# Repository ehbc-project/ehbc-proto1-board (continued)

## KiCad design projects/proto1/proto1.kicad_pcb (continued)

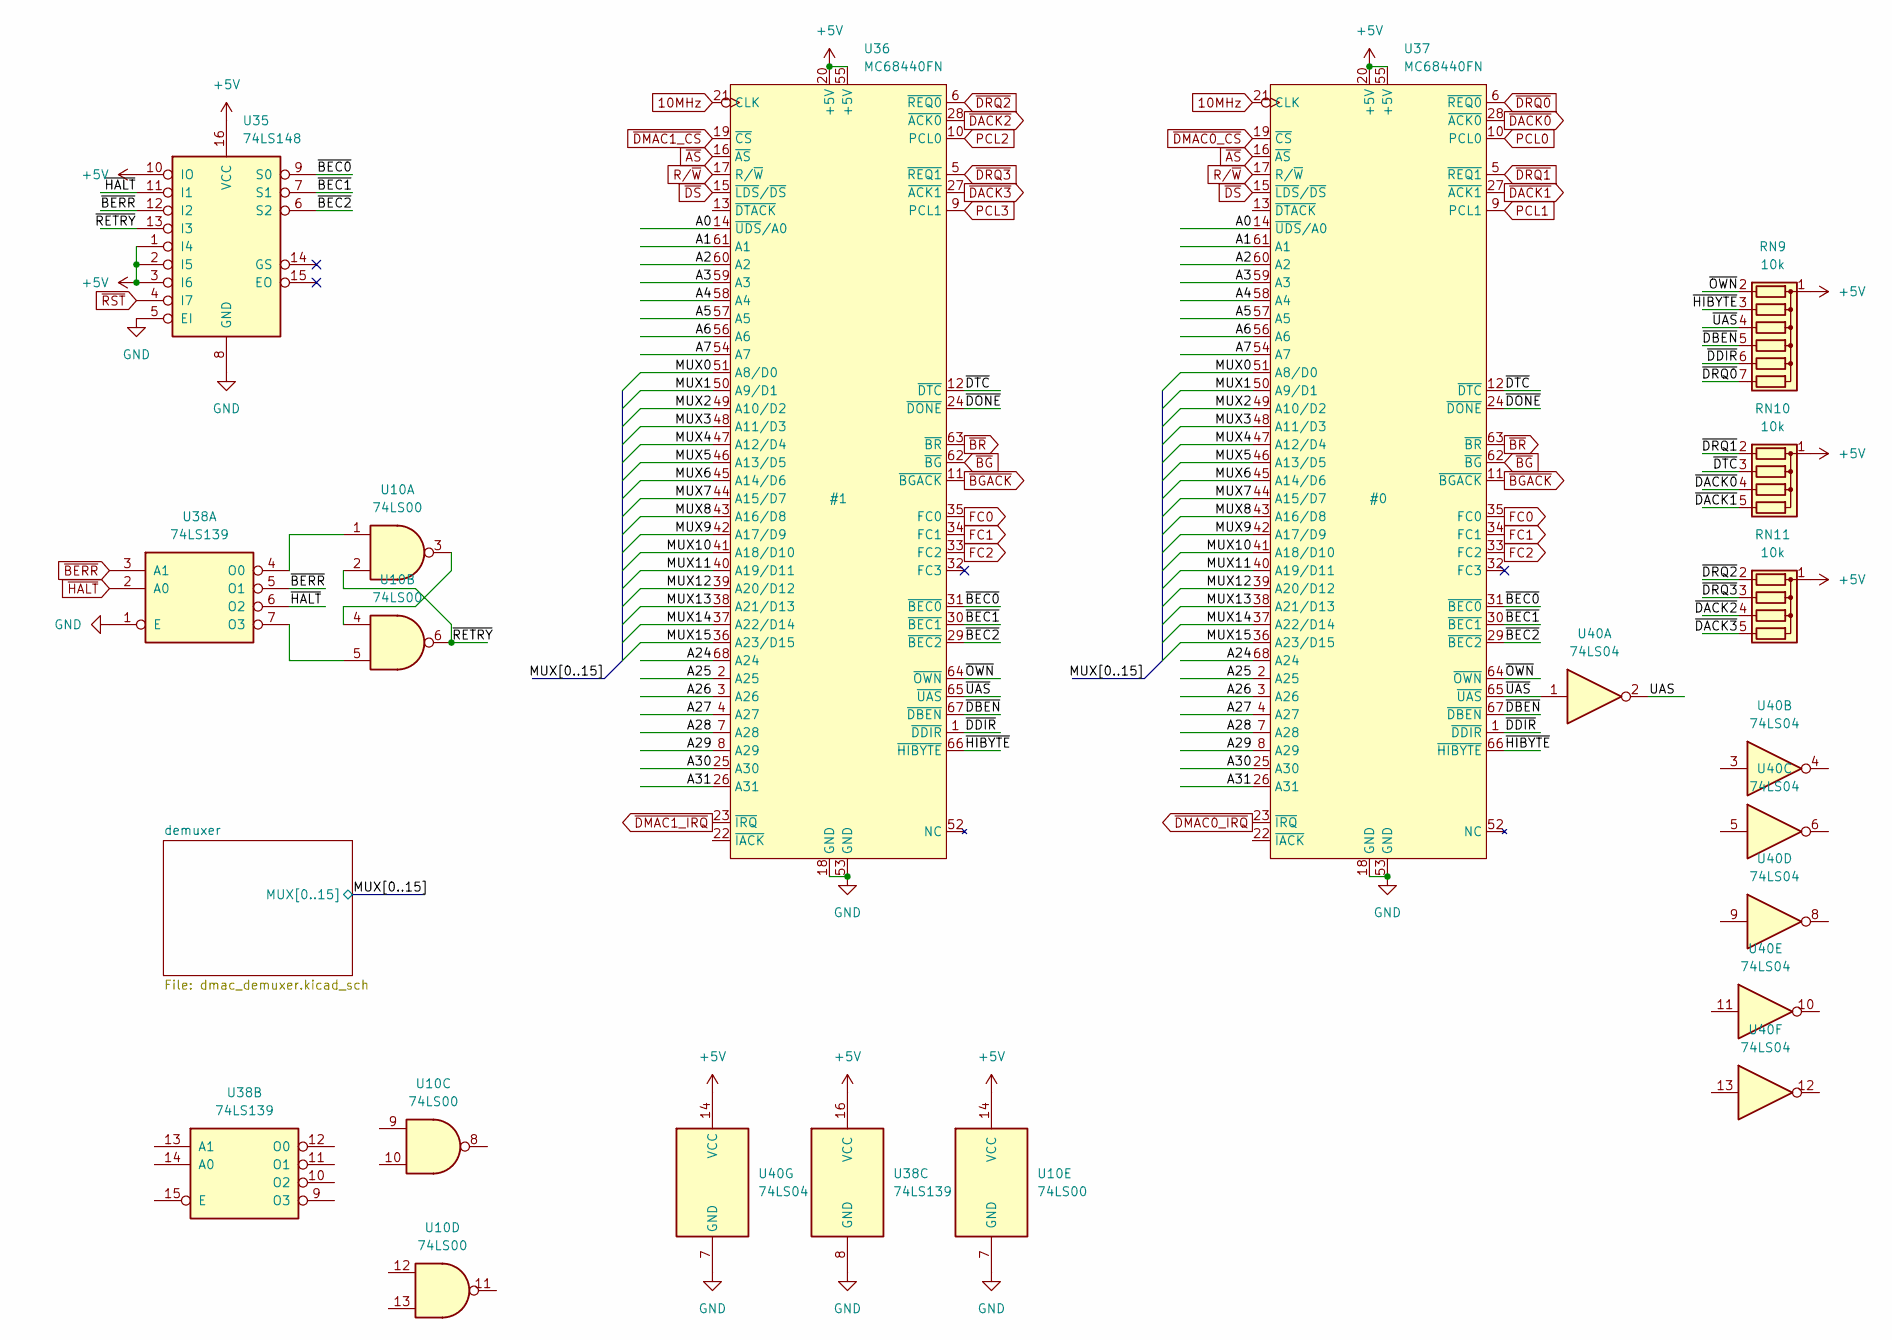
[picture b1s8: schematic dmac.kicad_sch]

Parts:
RN9: 10k; R_Array_SIP7
RN10, RN11: 10k; R_Array_SIP5
U10: 74LS00
U35: 74LS148; DIP-16_W7.62mm_Socket
U36, U37: MC68440FN; PLCC-68_THT-Socket
U38: 74LS139; DIP-16_W7.62mm_Socket
U40: 74LS04; DIP-14_W7.62mm_Socket

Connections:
10MHz: U36.21 (CLK), U37.21 (CLK); also elsewhere on the board
+5V: RN9.1 (common), RN10.1 (common), RN11.1 (common), U10.14 (VCC), U35.1 (I4), U35.2 (I5), U35.3 (I6), U35.10 (IO), U35.16 (VCC), U36.20 (+5V), U36.55 (+5V), U37.20 (+5V), U37.55 (+5V), U38.16 (VCC), U40.14 (VCC); also elsewhere on the board
/dmac/A0: U36.14 (~UDS/A0), U37.14 (~UDS/A0)
/dmac/A1: U36.61 (A1), U37.61 (A1)
/dmac/A2: U36.60 (A2), U37.60 (A2)
/dmac/A3: U36.59 (A3), U37.59 (A3)
/dmac/A4: U36.58 (A4), U37.58 (A4)
/dmac/A5: U36.57 (A5), U37.57 (A5)
/dmac/A6: U36.56 (A6), U37.56 (A6)
/dmac/A7: U36.54 (A7), U37.54 (A7)
/dmac/A24: U36.68 (A24), U37.68 (A24)
/dmac/A25: U36.2 (A25), U37.2 (A25)
/dmac/A26: U36.3 (A26), U37.3 (A26)
/dmac/A27: U36.4 (A27), U37.4 (A27)
/dmac/A28: U36.7 (A28), U37.7 (A28)
/dmac/A29: U36.8 (A29), U37.8 (A29)
/dmac/A30: U36.25 (A30), U37.25 (A30)
/dmac/A31: U36.26 (A31), U37.26 (A31)
/dmac/MUX0: U36.51 (A8/D0), U37.51 (A8/D0); also elsewhere on the board
/dmac/MUX1: U36.50 (A9/D1), U37.50 (A9/D1); also elsewhere on the board
/dmac/MUX2: U36.49 (A10/D2), U37.49 (A10/D2); also elsewhere on the board
/dmac/MUX3: U36.48 (A11/D3), U37.48 (A11/D3); also elsewhere on the board
/dmac/MUX4: U36.47 (A12/D4), U37.47 (A12/D4); also elsewhere on the board
/dmac/MUX5: U36.46 (A13/D5), U37.46 (A13/D5); also elsewhere on the board
/dmac/MUX6: U36.45 (A14/D6), U37.45 (A14/D6); also elsewhere on the board
/dmac/MUX7: U36.44 (A15/D7), U37.44 (A15/D7); also elsewhere on the board
/dmac/MUX8: U36.43 (A16/D8), U37.43 (A16/D8); also elsewhere on the board
/dmac/MUX9: U36.42 (A17/D9), U37.42 (A17/D9); also elsewhere on the board
/dmac/MUX10: U36.41 (A18/D10), U37.41 (A18/D10); also elsewhere on the board
/dmac/MUX11: U36.40 (A19/D11), U37.40 (A19/D11); also elsewhere on the board
/dmac/MUX12: U36.39 (A20/D12), U37.39 (A20/D12); also elsewhere on the board
/dmac/MUX13: U36.38 (A21/D13), U37.38 (A21/D13); also elsewhere on the board
/dmac/MUX14: U36.37 (A22/D14), U37.37 (A22/D14); also elsewhere on the board
/dmac/MUX15: U36.36 (A23/D15), U37.36 (A23/D15); also elsewhere on the board
/dmac/UAS: U40.2
/dmac/~BEC0: U35.9 (S0), U36.31 (~BEC0), U37.31 (~BEC0)
/dmac/~BEC1: U35.7 (S1), U36.30 (~BEC1), U37.30 (~BEC1)
/dmac/~BEC2: U35.6 (S2), U36.29 (~BEC2), U37.29 (~BEC2)
/dmac/~DBEN: RN9.5 (R4), U36.67 (~DBEN), U37.67 (~DBEN)
/dmac/~DDIR: RN9.6 (R5), U36.1 (~DDIR), U37.1 (~DDIR)
/dmac/~DONE: U36.24 (~DONE), U37.24 (~DONE)
/dmac/~DTC: RN10.3 (R2), U36.12 (~DTC), U37.12 (~DTC)
/dmac/~HIBYTE: RN9.3 (R2), U36.66 (~HIBYTE), U37.66 (~HIBYTE)
/dmac/~OWN: RN9.2 (R1), U36.64 (~OWN), U37.64 (~OWN)
/dmac/~RETRY: U10.2, U10.6, U35.13 (I3)
/dmac/~UAS: RN9.4 (R3), U36.65 (~UAS), U37.65 (~UAS), U40.1
FC0: U36.35 (FC0), U37.35 (FC0); also elsewhere on the board
FC1: U36.34 (FC1), U37.34 (FC1); also elsewhere on the board
FC2: U36.33 (FC2), U37.33 (FC2); also elsewhere on the board
GND: U10.7 (GND), U35.5 (EI), U35.8 (GND), U36.18 (GND), U36.53 (GND), U37.18 (GND), U37.53 (GND), U38.1 (E), U38.8 (GND), U40.7 (GND); also elsewhere on the board
unnamed: U10.3, U10.4
unnamed: U10.1, U38.4 (O0)
unnamed: U10.5, U38.7 (O3)
PCL0: U37.10 (PCL0)
PCL1: U37.9 (PCL1)
PCL2: U36.10 (PCL0)
PCL3: U36.9 (PCL1)
R/~W: U36.17 (R/~W), U37.17 (R/~W); also elsewhere on the board
~AS: U36.16 (~AS), U37.16 (~AS); also elsewhere on the board
~BERR: U35.12 (I2), U38.3 (A1), U38.5 (O1); also elsewhere on the board
~BGACK: U36.11 (~BGACK), U37.11 (~BGACK); also elsewhere on the board
~BG: U36.62 (~BG), U37.62 (~BG); also elsewhere on the board
~BR: U36.63 (~BR), U37.63 (~BR); also elsewhere on the board
~DACK0: RN10.4 (R3), U37.28 (~ACK0)
~DACK1: RN10.5 (R4), U37.27 (~ACK1)
~DACK2: RN11.4 (R3), U36.28 (~ACK0)
~DACK3: RN11.5 (R4), U36.27 (~ACK1)
~DMAC0_CS: U37.19 (~CS)
~DMAC0_IRQ: U37.23 (~IRQ); also elsewhere on the board
~DMAC1_CS: U36.19 (~CS)
~DMAC1_IRQ: U36.23 (~IRQ); also elsewhere on the board
~DRQ0: RN9.7 (R6), U37.6 (~REQ0)
~DRQ1: RN10.2 (R1), U37.5 (~REQ1)
~DRQ2: RN11.2 (R1), U36.6 (~REQ0)
~DRQ3: RN11.3 (R2), U36.5 (~REQ1)
~DS: U10.10, U36.15 (~LDS/~DS), U37.15 (~LDS/~DS); also elsewhere on the board
~DUART_CS: U10.9
~HALT: U35.11 (I1), U38.2 (A0), U38.6 (O2); also elsewhere on the board
~RST: U35.4 (I7); also elsewhere on the board

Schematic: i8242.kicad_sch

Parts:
C23: 100n; C_Disc_D4.3mm_W1.9mm_P5.00mm
J7: KMDGX-6SG_P-S4N; KMDGX6SGPS4N; Mouser Part Number 806-KMDGX-6SGP-S4N
U14: VT82C42; DIP-40_W15.24mm_Socket

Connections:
8MHz: U14.3 (XTAL2); also elsewhere on the board
+5V: C23.1, U14.40 (+5V); also elsewhere on the board
/i8242/BA0: U14.9 (A0)
/i8242/BD24: U14.12 (D0)
/i8242/BD25: U14.13 (D1)
/i8242/BD26: U14.14 (D2)
/i8242/BD27: U14.15 (D3)
/i8242/BD28: U14.16 (D4)
/i8242/BD29: U14.17 (D5)
/i8242/BD30: U14.18 (D6)
/i8242/BD31: U14.19 (D7)
GND: C23.2, U14.2 (XTAL1), U14.20 (GND); also elsewhere on the board
KB_IRQ: U14.35 (P24); also elsewhere on the board
MS_IRQ: U14.36 (P25); also elsewhere on the board
~I8242_CS: U14.6 (~CS)
~RD: U14.8 (~RD); also elsewhere on the board
~RST: U14.4 (~RST); also elsewhere on the board
~WR: U14.10 (~WR); also elsewhere on the board

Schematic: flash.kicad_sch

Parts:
C9, C10: 100n; C_Disc_D4.3mm_W1.9mm_P5.00mm
U7, U8: SST39SF040; DIP-32_W15.24mm_Socket

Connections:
+5V: C9.1, C10.1, U7.32 (VCC), U8.32 (VCC); also elsewhere on the board
A1: U7.12 (A0), U8.12 (A0); also elsewhere on the board
A2: U7.11 (A1), U8.11 (A1); also elsewhere on the board
A3: U7.10 (A2), U8.10 (A2); also elsewhere on the board
A4: U7.9 (A3), U8.9 (A3); also elsewhere on the board
A5: U7.8 (A4), U8.8 (A4); also elsewhere on the board
A6: U7.7 (A5), U8.7 (A5); also elsewhere on the board
A7: U7.6 (A6), U8.6 (A6); also elsewhere on the board
A8: U7.5 (A7), U8.5 (A7); also elsewhere on the board
A9: U7.27 (A8), U8.27 (A8); also elsewhere on the board
A10: U7.26 (A9), U8.26 (A9); also elsewhere on the board
A11: U7.23 (A10), U8.23 (A10); also elsewhere on the board
A12: U7.25 (A11), U8.25 (A11); also elsewhere on the board
A13: U7.4 (A12), U8.4 (A12); also elsewhere on the board
A14: U7.28 (A13), U8.28 (A13); also elsewhere on the board
A15: U7.29 (A14), U8.29 (A14); also elsewhere on the board
A16: U7.3 (A15), U8.3 (A15); also elsewhere on the board
A17: U7.2 (A16), U8.2 (A16); also elsewhere on the board
A18: U7.30 (A17), U8.30 (A17); also elsewhere on the board
A19: U7.1 (A18), U8.1 (A18); also elsewhere on the board
D16: U7.13 (D0); also elsewhere on the board
D17: U7.14 (D1); also elsewhere on the board
D18: U7.15 (D2); also elsewhere on the board
D19: U7.17 (D3); also elsewhere on the board
D20: U7.18 (D4); also elsewhere on the board
D21: U7.19 (D5); also elsewhere on the board
D22: U7.20 (D6); also elsewhere on the board
D23: U7.21 (D7); also elsewhere on the board
D24: U8.13 (D0); also elsewhere on the board
D25: U8.14 (D1); also elsewhere on the board
D26: U8.15 (D2); also elsewhere on the board
D27: U8.17 (D3); also elsewhere on the board
D28: U8.18 (D4); also elsewhere on the board
D29: U8.19 (D5); also elsewhere on the board
D30: U8.20 (D6); also elsewhere on the board
D31: U8.21 (D7); also elsewhere on the board
GND: C9.2, C10.2, U7.16 (GND), U7.24 (OE), U8.16 (GND), U8.24 (OE); also elsewhere on the board
~FLASH_CS: U7.22 (CE), U8.22 (CE)

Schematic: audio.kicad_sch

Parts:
C26, C27, C36, C37: 20p; C_Disc_D4.3mm_W1.9mm_P5.00mm
C28, C29, C32, C33, C34, C38, C40: 100n; C_Disc_D4.3mm_W1.9mm_P5.00mm
C30, C31, C35: 1u; CP_Radial_D5.0mm_P2.50mm
C39, C41: 10u; CP_Radial_D5.0mm_P2.50mm
C42, C43: 1n; C_Disc_D4.3mm_W1.9mm_P5.00mm
J11: AUDIO_DATA; PinHeader_2x05_P2.54mm_Vertical
J12: STX-4335-5BGP-S1; STX43355BGPS1; Mouser Part Number 806-STX-43355BGPS1
L1: L; L_Axial_L9.5mm_D4.0mm_P5.08mm_Vertical_Fastron_SMCC
R5: 2; R_Axial_DIN0204_L3.6mm_D1.6mm_P7.62mm_Horizontal
RN8: 33; DIP-8_W7.62mm
U26: CS4231A; PLCC-68_THT-Socket
Y2: 24.576M; Crystal_HC49-4H_Vertical
Y3: 16.9344M; Crystal_HC49-4H_Vertical

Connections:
+5V: C28.2, C29.2, C30.1, C31.1, J11.1, L1.1, U26.1 (VD1), U26.7 (VD2), U26.23 (~PDWN); also elsewhere on the board
+5VA: C34.1, C35.1, R5.2, U26.35 (VA1), U26.36 (VA2); also elsewhere on the board
/audio/BLUE_RING: J12.35; also elsewhere on the board
/audio/BLUE_TIP: J12.32; also elsewhere on the board
/audio/LIME_RING: J12.25; also elsewhere on the board
/audio/LIME_TIP: J12.22; also elsewhere on the board
/audio/LLINE: U26.30 (LLINE); also elsewhere on the board
/audio/LMIC: U26.29 (LMIC); also elsewhere on the board
/audio/PINK_RING: J12.5; also elsewhere on the board
/audio/PINK_TIP: J12.2; also elsewhere on the board
/audio/PWR1: C32.2, C33.2, L1.2, R5.1, U26.15 (VD3), U26.19 (VD4)
/audio/RLINE: U26.27 (RLINE); also elsewhere on the board
/audio/RMIC: U26.28 (RMIC); also elsewhere on the board
/audio/VREF: C40.2, C41.1, U26.32 (VREF); also elsewhere on the board
/audio/VREFI: C38.2, C39.1, U26.33 (VREFI)
/audio/XTAL1I: C36.2, U26.17 (XTAL1I), Y2.1
/audio/XTAL1O: C26.1, U26.18 (XTAL1O), Y2.2
/audio/XTAL2I: C37.2, U26.21 (XTAL2I), Y3.1
/audio/XTAL2O: C27.1, U26.22 (XTAL2O), Y3.2
AUDIO_IRQ: U26.57 (IRQ); also elsewhere on the board
BA0: U26.10 (A0); also elsewhere on the board
BA1: U26.9 (A1); also elsewhere on the board
BD24: U26.6 (D0); also elsewhere on the board
BD25: U26.5 (D1); also elsewhere on the board
BD26: U26.4 (D2); also elsewhere on the board
BD27: U26.3 (D3); also elsewhere on the board
BD28: U26.68 (D4); also elsewhere on the board
BD29: U26.67 (D5); also elsewhere on the board
BD30: U26.66 (D6); also elsewhere on the board
BD31: U26.65 (D7); also elsewhere on the board
GND: C26.2, C27.2, C28.1, C29.1, C30.2, C31.2, C36.1, C37.1, J11.2, J11.4, J11.6, J11.8, J11.10, U26.2 (DGND1), U26.8 (DGND2), U26.16 (DGND3), U26.20 (DGND4), U26.53 (DGND7), U26.55 (TEST), U26.64 (DGND8); also elsewhere on the board
GNDA: C32.1, C33.1, C34.2, C35.2, C38.1, C39.2, C40.1, C41.2, C42.2, C43.2, J12.1, J12.3, J12.4, J12.23, J12.24, J12.33, J12.34, J12.MH1, J12.MH2, J12.MH3, J12.MH4, U26.34 (AGND1), U26.37 (AGND2); also elsewhere on the board
unnamed: J11.3, RN8.8 (R1.2)
unnamed: J11.5, RN8.7 (R2.2)
unnamed: J11.7, RN8.6 (R3.2)
unnamed: J11.9, RN8.5 (R4.2)
unnamed: RN8.1 (R1.1), U26.52 (SDOUT)
unnamed: RN8.2 (R2.1), U26.51 (SCLK)
unnamed: RN8.3 (R3.1), U26.50 (FSYNC)
unnamed: RN8.4 (R4.1), U26.49 (SDIN)
unnamed: C43.1, U26.31 (LFILT)
unnamed: C42.1, U26.26 (RFILT)
~AUDIO_CS: U26.59 (~CS)
~RD: U26.60 (~RD); also elsewhere on the board
~WR: U26.61 (~WR); also elsewhere on the board

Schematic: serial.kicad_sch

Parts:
C11, C12, C14, C15, C16, C17, C18, C19: 1u; C_Disc_D4.3mm_W1.9mm_P5.00mm
C13: 100n; C_Disc_D4.3mm_W1.9mm_P5.00mm
J4, J5: 5747840-4; 57478404; Mouser Part Number 571-5747840-4
U9, U12: MAX232; DIP-16_W7.62mm_Socket
U11: MC68681P; DIP-40_W15.24mm_Socket

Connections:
3.6864MHz: U11.33 (X2); also elsewhere on the board
+5V: C13.1, U9.16 (VCC), U11.40 (VCC), U12.16 (VCC); also elsewhere on the board
/serial/RxDA: U9.12 (R1OUT), U11.31 (RxDA)
/serial/RxDB: U11.10 (RxDB), U12.12 (R1OUT)
/serial/RxDP1: J4.2, U9.13 (R1IN)
/serial/RxDP2: J5.2, U12.13 (R1IN)
/serial/TxDA: U9.11 (T1IN), U11.30 (TxDA)
/serial/TxDB: U11.11 (TxDB), U12.11 (T1IN)
/serial/TxDP1: J4.3, U9.14 (T1OUT)
/serial/TxDP2: J5.3, U12.14 (T1OUT)
/serial/~CTSA: U9.9 (R2OUT), U11.7 (IP0)
/serial/~CTSB: U11.4 (IP1), U12.9 (R2OUT)
/serial/~CTSP1: J4.8, U9.8 (R2IN)
/serial/~CTSP2: J5.8, U12.8 (R2IN)
/serial/~RTSA: U9.10 (T2IN), U11.29 (OP0)
/serial/~RTSB: U11.12 (OP1), U12.10 (T2IN)
/serial/~RTSP1: J4.7, U9.7 (T2OUT)
/serial/~RTSP2: J5.7, U12.7 (T2OUT)
BA0: U11.1 (RS1); also elsewhere on the board
BA1: U11.3 (RS2); also elsewhere on the board
BA2: U11.5 (RS3); also elsewhere on the board
BA3: U11.6 (RS4); also elsewhere on the board
BD24: U11.25 (D0); also elsewhere on the board
BD25: U11.16 (D1); also elsewhere on the board
BD26: U11.24 (D2); also elsewhere on the board
BD27: U11.17 (D3); also elsewhere on the board
BD28: U11.23 (D4); also elsewhere on the board
BD29: U11.18 (D5); also elsewhere on the board
BD30: U11.22 (D6); also elsewhere on the board
BD31: U11.19 (D7); also elsewhere on the board
GND: C13.2, C14.2, C15.2, C18.2, C19.2, J4.5, J5.5, U9.15 (GND), U11.20 (GND), U12.15 (GND); also elsewhere on the board
unnamed: C11.1, U9.1 (C1+)
unnamed: C11.2, U9.3 (C1-)
unnamed: C12.1, U9.4 (C2+)
unnamed: C12.2, U9.5 (C2-)
unnamed: C14.1, U9.2 (VS+)
unnamed: C15.1, U9.6 (VS-)
unnamed: C16.1, U12.1 (C1+)
unnamed: C16.2, U12.3 (C1-)
unnamed: C17.1, U12.4 (C2+)
unnamed: C17.2, U12.5 (C2-)
unnamed: C18.1, U12.2 (VS+)
unnamed: C19.1, U12.6 (VS-)
R/~W: U11.8 (R/~W); also elsewhere on the board
~DSACK0: U11.9 (~DTACK); also elsewhere on the board
~DUART_IRQ: U11.21 (~IRQ); also elsewhere on the board
~RST: U11.34 (~RST); also elsewhere on the board

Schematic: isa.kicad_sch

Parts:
J1, J2, J3: Bus_ISA_16bit; ATA_16bit
RN3: 10k; R_Array_SIP10
RN4: 4.7k; R_Array_SIP8
RN5, RN6: 4.7k; R_Array_SIP7

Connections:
8MHz: J1.20 (CLK), J2.20 (CLK), J3.20 (CLK); also elsewhere on the board
14.31818MHz: J1.30 (OSC), J2.30 (OSC), J3.30 (OSC); also elsewhere on the board
+5V: J1.3 (+5V), J1.29 (VCC), J1.78 (+5V), J2.3 (+5V), J2.29 (VCC), J2.78 (+5V), J3.3 (+5V), J3.29 (VCC), J3.78 (+5V), RN3.1 (common); also elsewhere on the board
+12V: J1.9 (+12V), J2.9 (+12V), J3.9 (+12V); also elsewhere on the board
-12V: J1.7 (-12V), J2.7 (-12V), J3.7 (-12V); also elsewhere on the board
/isa/ALE: J1.28 (ALE), J2.28 (ALE), J3.28 (ALE)
/isa/BA0: J1.62 (BA00), J2.62 (BA00), J3.62 (BA00); also elsewhere on the board
/isa/BA1: J1.61 (BA01), J2.61 (BA01), J3.61 (BA01); also elsewhere on the board
/isa/BA2: J1.60 (BA02), J2.60 (BA02), J3.60 (BA02); also elsewhere on the board
/isa/BA3: J1.59 (BA03), J2.59 (BA03), J3.59 (BA03); also elsewhere on the board
/isa/BA4: J1.58 (BA04), J2.58 (BA04), J3.58 (BA04); also elsewhere on the board
/isa/BA5: J1.57 (BA05), J2.57 (BA05), J3.57 (BA05); also elsewhere on the board
/isa/BA6: J1.56 (BA06), J2.56 (BA06), J3.56 (BA06); also elsewhere on the board
/isa/BA7: J1.55 (BA07), J2.55 (BA07), J3.55 (BA07); also elsewhere on the board
/isa/BA8: J1.54 (BA08), J2.54 (BA08), J3.54 (BA08); also elsewhere on the board
/isa/BA9: J1.53 (BA09), J2.53 (BA09), J3.53 (BA09); also elsewhere on the board
/isa/BA10: J1.52 (BA10), J2.52 (BA10), J3.52 (BA10); also elsewhere on the board
/isa/BA11: J1.51 (BA11), J2.51 (BA11), J3.51 (BA11); also elsewhere on the board
/isa/BA12: J1.50 (BA12), J2.50 (BA12), J3.50 (BA12); also elsewhere on the board
/isa/BA13: J1.49 (BA13), J2.49 (BA13), J3.49 (BA13); also elsewhere on the board
/isa/BA14: J1.48 (BA14), J2.48 (BA14), J3.48 (BA14); also elsewhere on the board
/isa/BA15: J1.47 (BA15), J2.47 (BA15), J3.47 (BA15); also elsewhere on the board
/isa/BA16: J1.46 (BA16), J2.46 (BA16), J3.46 (BA16); also elsewhere on the board
/isa/BA17: J1.45 (BA17), J1.88 (LA17), J2.45 (BA17), J2.88 (LA17), J3.45 (BA17), J3.88 (LA17); also elsewhere on the board
/isa/BA18: J1.44 (BA18), J1.87 (LA18), J2.44 (BA18), J2.87 (LA18), J3.44 (BA18), J3.87 (LA18); also elsewhere on the board
/isa/BA19: J1.43 (BA19), J1.86 (LA19), J2.43 (BA19), J2.86 (LA19), J3.43 (BA19), J3.86 (LA19); also elsewhere on the board
/isa/BA20: J1.85 (LA20), J2.85 (LA20), J3.85 (LA20); also elsewhere on the board
/isa/BA21: J1.84 (LA21), J2.84 (LA21), J3.84 (LA21); also elsewhere on the board
/isa/BA22: J1.83 (LA22), J2.83 (LA22), J3.83 (LA22); also elsewhere on the board
/isa/BA23: J1.82 (LA23), J2.82 (LA23), J3.82 (LA23); also elsewhere on the board
/isa/BD0: J1.40 (DB0), J2.40 (DB0), J3.40 (DB0); also elsewhere on the board
/isa/BD1: J1.39 (DB1), J2.39 (DB1), J3.39 (DB1); also elsewhere on the board
/isa/BD2: J1.38 (DB2), J2.38 (DB2), J3.38 (DB2); also elsewhere on the board
/isa/BD3: J1.37 (DB3), J2.37 (DB3), J3.37 (DB3); also elsewhere on the board
/isa/BD4: J1.36 (DB4), J2.36 (DB4), J3.36 (DB4); also elsewhere on the board
/isa/BD5: J1.35 (DB5), J2.35 (DB5), J3.35 (DB5); also elsewhere on the board
/isa/BD6: J1.34 (DB6), J2.34 (DB6), J3.34 (DB6); also elsewhere on the board
/isa/BD7: J1.33 (DB7), J2.33 (DB7), J3.33 (DB7); also elsewhere on the board
/isa/BD8: J1.91 (D8), J2.91 (D8), J3.91 (D8); also elsewhere on the board
/isa/BD9: J1.92 (D9), J2.92 (D9), J3.92 (D9); also elsewhere on the board
/isa/BD10: J1.93 (D10), J2.93 (D10), J3.93 (D10); also elsewhere on the board
/isa/BD11: J1.94 (D11), J2.94 (D11), J3.94 (D11); also elsewhere on the board
/isa/BD12: J1.95 (D12), J2.95 (D12), J3.95 (D12); also elsewhere on the board
/isa/BD13: J1.96 (D13), J2.96 (D13), J3.96 (D13); also elsewhere on the board
/isa/BD14: J1.97 (D14), J2.97 (D14), J3.97 (D14); also elsewhere on the board
/isa/BD15: J1.98 (D15), J2.98 (D15), J3.98 (D15); also elsewhere on the board
/isa/DRQ0: J1.71 (DRQ0), J2.71 (DRQ0), J3.71 (DRQ0), RN4.5 (R4)
/isa/DRQ1: J1.18 (DRQ1), J2.18 (DRQ1), J3.18 (DRQ1), RN4.6 (R5)
/isa/DRQ2: J1.6 (DRQ2), J2.6 (DRQ2), J3.6 (DRQ2), RN4.7 (R6)
/isa/DRQ3: J1.16 (DRQ3), J2.16 (DRQ3), J3.16 (DRQ3), RN4.8 (R7)
/isa/DRQ5: J1.73 (DRQ5), J2.73 (DRQ5), J3.73 (DRQ5), RN4.4 (R3)
/isa/DRQ6: J1.75 (DRQ6), J2.75 (DRQ6), J3.75 (DRQ6), RN4.3 (R2)
/isa/DRQ7: J1.77 (DRQ7), J2.77 (DRQ7), J3.77 (DRQ7), RN4.2 (R1)
/isa/IOCHRDY: J1.41 (IO_READY), J2.41 (IO_READY), J3.41 (IO_READY); also elsewhere on the board
/isa/SBHE: J1.81 (SBHE), J2.81 (SBHE), J3.81 (SBHE)
/isa/~DACK0: J1.70 (~DACK0), J2.70 (~DACK0), J3.70 (~DACK0), RN3.5 (R4)
/isa/~DACK1: J1.17 (~DACK1), J2.17 (~DACK1), J3.17 (~DACK1), RN3.8 (R7)
/isa/~DACK2: J1.26 (~DACK2), J2.26 (~DACK2), J3.26 (~DACK2), RN3.6 (R5)
/isa/~DACK3: J1.15 (~DACK3), J2.15 (~DACK3), J3.15 (~DACK3), RN3.9 (R8)
/isa/~DACK5: J1.72 (~DACK5), J2.72 (~DACK5), J3.72 (~DACK5), RN3.4 (R3)
/isa/~DACK6: J1.74 (~DACK6), J2.74 (~DACK6), J3.74 (~DACK6), RN3.3 (R2)
/isa/~DACK7: J1.76 (~DACK7), J2.76 (~DACK7), J3.76 (~DACK7), RN3.2 (R1)
/isa/~IOCHCK: J1.32 (IO), J2.32 (IO), J3.32 (IO)
/isa/~IOCS16: J1.64 (~IOCS16), J2.64 (~IOCS16), J3.64 (~IOCS16); also elsewhere on the board
/isa/~IOR: J1.14 (~IOR), J2.14 (~IOR), J3.14 (~IOR)
/isa/~IOW: J1.13 (~IOW), J2.13 (~IOW), J3.13 (~IOW)
/isa/~MASTER: J1.79 (MASTER), J2.79 (MASTER), J3.79 (MASTER), RN3.10 (R9)
/isa/~MEMCS16: J1.63 (~MEMCS16), J2.63 (~MEMCS16), J3.63 (~MEMCS16)
/isa/~MEMR: J1.89 (~MEMR), J2.89 (~MEMR), J3.89 (~MEMR)
/isa/~MEMW: J1.90 (~MEMW), J2.90 (~MEMW), J3.90 (~MEMW)
/isa/~NOWS: J1.8 (UNUSED), J2.8 (UNUSED), J3.8 (UNUSED)
/isa/~REFRESH: J1.19 (~REFRESH), J2.19 (~REFRESH), J3.19 (~REFRESH), RN3.7 (R6)
/isa/~SMEMR: J1.12 (~SMEMR), J2.12 (~SMEMR), J3.12 (~SMEMR)
/isa/~SMEMW: J1.11 (~SMEMW), J2.11 (~SMEMW), J3.11 (~SMEMW)
GND: J1.1 (GND), J1.10 (GND), J1.31 (GND), J1.42 (AEN), J1.80 (GND), J2.1 (GND), J2.10 (GND), J2.31 (GND), J2.42 (AEN), J2.80 (GND), J3.1 (GND), J3.10 (GND), J3.31 (GND), J3.42 (AEN), J3.80 (GND), RN4.1 (common), RN5.1 (common), RN6.1 (common); also elsewhere on the board
IRQ2: J1.4 (IRQ2), J2.4 (IRQ2), J3.4 (IRQ2), RN5.7 (R6); also elsewhere on the board
IRQ3: J1.25 (IRQ3), J2.25 (IRQ3), J3.25 (IRQ3), RN5.2 (R1); also elsewhere on the board
IRQ4: J1.24 (IRQ4), J2.24 (IRQ4), J3.24 (IRQ4), RN5.3 (R2); also elsewhere on the board
IRQ5: J1.23 (IRQ5), J2.23 (IRQ5), J3.23 (IRQ5), RN5.4 (R3); also elsewhere on the board
IRQ6: J1.22 (IRQ6), J2.22 (IRQ6), J3.22 (IRQ6), RN5.5 (R4); also elsewhere on the board
IRQ7: J1.21 (IRQ7), J2.21 (IRQ7), J3.21 (IRQ7), RN5.6 (R5); also elsewhere on the board
IRQ10: J1.65 (IRQ10), J2.65 (IRQ10), J3.65 (IRQ10), RN6.6 (R5); also elsewhere on the board
IRQ11: J1.66 (IRQ11), J2.66 (IRQ11), J3.66 (IRQ11), RN6.5 (R4); also elsewhere on the board
IRQ12: J1.67 (IRQ12), J2.67 (IRQ12), J3.67 (IRQ12), RN6.4 (R3); also elsewhere on the board
IRQ14: J1.69 (IRQ14), J2.69 (IRQ14), J3.69 (IRQ14), RN6.2 (R1); also elsewhere on the board
IRQ15: J1.68 (IRQ15), J2.68 (IRQ15), J3.68 (IRQ15), RN6.3 (R2); also elsewhere on the board
RST: J1.2 (RESET), J2.2 (RESET), J3.2 (RESET); also elsewhere on the board

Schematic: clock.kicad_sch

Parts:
C24: 47n; C_Disc_D4.3mm_W1.9mm_P5.00mm
U15: MX8315MC; DIP-14_W7.62mm_Socket
X1: 10M; Oscillator_DIP-14
X2: 4M; Oscillator_DIP-14
X3: 3.6864M; Oscillator_DIP-14
X4: 8M; Oscillator_DIP-14
Y1: 14.31818M; Crystal_HC49-4H_Vertical

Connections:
3.6864MHz: X3.8 (OUT); also elsewhere on the board
4MHz: X2.8 (OUT); also elsewhere on the board
8MHz: X4.8 (OUT); also elsewhere on the board
10MHz: X1.8 (OUT); also elsewhere on the board
14.31818MHz: U15.4 (XCK); also elsewhere on the board
24MHz: U15.5 (PCK); also elsewhere on the board
+5V: U15.9 (DVDD), U15.14 (AVDD), X1.14 (Vcc); also elsewhere on the board
FREQ_SEL0: U15.11 (S0)
FREQ_SEL1: U15.12 (S1)
FREQ_SEL2: U15.13 (S2)
GND: C24.2, U15.1 (AGND), U15.7 (DGND), X1.7 (GND); also elsewhere on the board
unnamed: C24.1, U15.10 (CAP)
PROC_CLK: U15.8 (CK); also elsewhere on the board

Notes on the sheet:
MC68030@25/33/50MHz MC68882@=MC68030 MC68681@3.6864MHz MC68901@=MC68681 MC68440@10MHz MC146818@32.768kHz PC8477BV@24MHz VT82C42@12MHz MX8315MC@14.31818MHz ISABUS@8MHz 3.6864MHz 14.31818MHz -> 25/33/50Mhz, 12MHz, 24MHz, 8MHz 32.768kHz 10MHz

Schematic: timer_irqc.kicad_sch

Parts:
J9: TIMER0-3; PinHeader_1x05_P2.54mm_Vertical
J10: TIMER4-7; PinHeader_1x05_P2.54mm_Vertical
RN7: 10k; R_Array_SIP9
U20: 74LS348; DIP-16_W7.62mm_Socket
U21, U22: MC68901P; DIP-48_W15.24mm_Socket

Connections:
3.6864MHz: U21.17 (XTAL1), U22.17 (XTAL1); also elsewhere on the board
4MHz: U21.35 (CLK), U22.35 (CLK); also elsewhere on the board
+5V: RN7.1 (common), U20.10 (0), U20.16 (VCC), U21.11 (VCC), U22.11 (VCC); also elsewhere on the board
/timer_irqc/T0OUT: J9.1
/timer_irqc/T1OUT: J9.2
/timer_irqc/T2OUT: J9.3
/timer_irqc/T3OUT: J9.4
/timer_irqc/T4OUT: J10.1
/timer_irqc/T5OUT: J10.2
/timer_irqc/T6OUT: J10.3
/timer_irqc/T7OUT: J10.4
/timer_irqc/~IEO0: U21.33 (~IEO), U22.34 (~IEI)
/timer_irqc/~IRQ0: RN7.2 (R1)
/timer_irqc/~IRQ1: RN7.3 (R2), U20.11 (1)
/timer_irqc/~IRQ7: RN7.9 (R8), U20.4 (7)
AUDIO_IRQ: RN7.5 (R4), U20.13 (3); also elsewhere on the board
BA0: U21.2 (RS1), U22.2 (RS1); also elsewhere on the board
BA1: U21.3 (RS2), U22.3 (RS2); also elsewhere on the board
BA2: U21.4 (RS3), U22.4 (RS3); also elsewhere on the board
BA3: U21.5 (RS4), U22.5 (RS4); also elsewhere on the board
BA4: U21.6 (RS5), U22.6 (RS5)
BD24: U21.37 (D0), U22.37 (D0); also elsewhere on the board
BD25: U21.38 (D1), U22.38 (D1); also elsewhere on the board
BD26: U21.39 (D2), U22.39 (D2); also elsewhere on the board
BD27: U21.40 (D3), U22.40 (D3); also elsewhere on the board
BD28: U21.41 (D4), U22.41 (D4); also elsewhere on the board
BD29: U21.42 (D5), U22.42 (D5); also elsewhere on the board
BD30: U21.43 (D6), U22.43 (D6); also elsewhere on the board
BD31: U21.44 (D7), U22.44 (D7); also elsewhere on the board
FDC_IRQ: U21.29 (I7)
GND: J9.5, J10.5, U20.5 (EI), U20.8 (GND), U21.34 (~IEI), U21.36 (GND), U22.36 (GND); also elsewhere on the board
IDE_IRQ: U21.28 (I6)
IRQ2: U21.27 (I5); also elsewhere on the board
IRQ3: U22.26 (I4); also elsewhere on the board
IRQ4: U22.25 (I3); also elsewhere on the board
IRQ5: U22.24 (I2); also elsewhere on the board
IRQ6: U22.23 (I1); also elsewhere on the board
IRQ7: U22.22 (I0); also elsewhere on the board
IRQ10: U21.26 (I4); also elsewhere on the board
IRQ11: U21.25 (I3); also elsewhere on the board
IRQ12: U21.24 (I2); also elsewhere on the board
IRQ14: U21.23 (I1); also elsewhere on the board
IRQ15: U21.22 (I0); also elsewhere on the board
KB_IRQ: U22.29 (I7); also elsewhere on the board
MS_IRQ: U22.28 (I6); also elsewhere on the board
R/~W: U21.1 (R/~W), U22.1 (R/~W); also elsewhere on the board
~DMAC0_IRQ: RN7.7 (R6), U20.2 (5); also elsewhere on the board
~DMAC1_IRQ: RN7.6 (R5), U20.1 (4); also elsewhere on the board
~DSACK0: U21.46 (~DTACK), U22.46 (~DTACK); also elsewhere on the board
~DS: U21.47 (~DS), U22.47 (~DS); also elsewhere on the board
~DUART_IRQ: U22.27 (I5); also elsewhere on the board
~IPL0: U20.9 (A0); also elsewhere on the board
~IPL1: U20.7 (A1); also elsewhere on the board
~IPL2: U20.6 (A2); also elsewhere on the board
~MFP0_CS: U21.48 (~CS)
~MFP1_CS: U22.48 (~CS)
~MFP_IRQ: RN7.4 (R3), U20.12 (2), U21.32 (~IRQ), U22.32 (~IRQ)
~RST: U21.21 (~RST), U22.21 (~RST); also elsewhere on the board
~RTC_IRQ: RN7.8 (R7), U20.3 (6); also elsewhere on the board

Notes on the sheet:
PRIORITY: - MC68440 #0 - MC68440 #1 - MC68901 #0: - - PC8477BV - - IDE - - Timer 0 - - Timer 1 - - ISA INT2 - - ISA INT10 - - Timer 2 - - Timer 3 - - ISA INT11 - - ISA INT12 - - ISA INT14 - - ISA INT15 - MC68901 #1: - - VT82C42 KB - - VT82C42 MS - - Timer 4 - - Timer 5 - - MC68681 - - ISA INT3 - - 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

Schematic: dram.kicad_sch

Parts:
U3, U4, U5, U6: SIMM72

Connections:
+5V: U3.10 (+5V), U3.30 (+5V), U3.59 (+5V), U4.10 (+5V), U4.30 (+5V), U4.59 (+5V), U5.10 (+5V), U5.30 (+5V), U5.59 (+5V), U6.10 (+5V), U6.30 (+5V), U6.59 (+5V); also elsewhere on the board
/dram/~CAS0: U3.40 (~CAS0), U4.40 (~CAS0), U5.40 (~CAS0), U6.40 (~CAS0)
/dram/~CAS1: U3.43 (~CAS1), U4.43 (~CAS1), U5.43 (~CAS1), U6.43 (~CAS1)
/dram/~CAS2: U3.41 (~CAS2), U4.41 (~CAS2), U5.41 (~CAS2), U6.41 (~CAS2)
/dram/~CAS3: U3.42 (~CAS3), U4.42 (~CAS3), U5.42 (~CAS3), U6.42 (~CAS3)
/dram/~RAS0: U6.33 (~RAS2), U6.44 (~RAS0)
/dram/~RAS1: U6.34 (~RAS3), U6.45 (~RAS1)
/dram/~RAS2: U5.33 (~RAS2), U5.44 (~RAS0)
/dram/~RAS3: U5.34 (~RAS3), U5.45 (~RAS1)
/dram/~RAS4: U4.33 (~RAS2), U4.44 (~RAS0)
/dram/~RAS5: U4.34 (~RAS3), U4.45 (~RAS1)
/dram/~RAS6: U3.33 (~RAS2), U3.44 (~RAS0)
/dram/~RAS7: U3.34 (~RAS3), U3.45 (~RAS1)
/dram/~WE: U3.47 (~WE), U4.47 (~WE), U5.47 (~WE), U6.47 (~WE)
D0: U3.2 (DQ0), U4.2 (DQ0), U5.2 (DQ0), U6.2 (DQ0); also elsewhere on the board
D1: U3.4 (DQ1), U4.4 (DQ1), U5.4 (DQ1), U6.4 (DQ1); also elsewhere on the board
D2: U3.6 (DQ2), U4.6 (DQ2), U5.6 (DQ2), U6.6 (DQ2); also elsewhere on the board
D3: U3.8 (DQ3), U4.8 (DQ3), U5.8 (DQ3), U6.8 (DQ3); also elsewhere on the board
D4: U3.20 (DQ4), U4.20 (DQ4), U5.20 (DQ4), U6.20 (DQ4); also elsewhere on the board
D5: U3.22 (DQ5), U4.22 (DQ5), U5.22 (DQ5), U6.22 (DQ5); also elsewhere on the board
D6: U3.24 (DQ6), U4.24 (DQ6), U5.24 (DQ6), U6.24 (DQ6); also elsewhere on the board
D7: U3.26 (DQ7), U4.26 (DQ7), U5.26 (DQ7), U6.26 (DQ7); also elsewhere on the board
D8: U3.49 (DQ8), U4.49 (DQ8), U5.49 (DQ8), U6.49 (DQ8); also elsewhere on the board
D9: U3.51 (DQ9), U4.51 (DQ9), U5.51 (DQ9), U6.51 (DQ9); also elsewhere on the board
D10: U3.53 (DQ10), U4.53 (DQ10), U5.53 (DQ10), U6.53 (DQ10); also elsewhere on the board
D11: U3.55 (DQ11), U4.55 (DQ11), U5.55 (DQ11), U6.55 (DQ11); also elsewhere on the board
D12: U3.57 (DQ12), U4.57 (DQ12), U5.57 (DQ12), U6.57 (DQ12); also elsewhere on the board
D13: U3.61 (DQ13), U4.61 (DQ13), U5.61 (DQ13), U6.61 (DQ13); also elsewhere on the board
D14: U3.63 (DQ14), U4.63 (DQ14), U5.63 (DQ14), U6.63 (DQ14); also elsewhere on the board
D15: U3.65 (DQ15), U4.65 (DQ15), U5.65 (DQ15), U6.65 (DQ15); also elsewhere on the board
D16: U3.3 (DQ16), U4.3 (DQ16), U5.3 (DQ16), U6.3 (DQ16); also elsewhere on the board
D17: U3.5 (DQ17), U4.5 (DQ17), U5.5 (DQ17), U6.5 (DQ17); also elsewhere on the board
D18: U3.7 (DQ18), U4.7 (DQ18), U5.7 (DQ18), U6.7 (DQ18); also elsewhere on the board
D19: U3.9 (DQ19), U4.9 (DQ19), U5.9 (DQ19), U6.9 (DQ19); also elsewhere on the board
D20: U3.21 (DQ20), U4.21 (DQ20), U5.21 (DQ20), U6.21 (DQ20); also elsewhere on the board
D21: U3.23 (DQ21), U4.23 (DQ21), U5.23 (DQ21), U6.23 (DQ21); also elsewhere on the board
D22: U3.25 (DQ22), U4.25 (DQ22), U5.25 (DQ22), U6.25 (DQ22); also elsewhere on the board
D23: U3.27 (DQ23), U4.27 (DQ23), U5.27 (DQ23), U6.27 (DQ23); also elsewhere on the board
D24: U3.50 (DQ24), U4.50 (DQ24), U5.50 (DQ24), U6.50 (DQ24); also elsewhere on the board
D25: U3.52 (DQ25), U4.52 (DQ25), U5.52 (DQ25), U6.52 (DQ25); also elsewhere on the board
D26: U3.54 (DQ26), U4.54 (DQ26), U5.54 (DQ26), U6.54 (DQ26); also elsewhere on the board
D27: U3.56 (DQ27), U4.56 (DQ27), U5.56 (DQ27), U6.56 (DQ27); also elsewhere on the board
D28: U3.58 (DQ28), U4.58 (DQ28), U5.58 (DQ28), U6.58 (DQ28); also elsewhere on the board
D29: U3.60 (DQ29), U4.60 (DQ29), U5.60 (DQ29), U6.60 (DQ29); also elsewhere on the board
D30: U3.62 (DQ30), U4.62 (DQ30), U5.62 (DQ30), U6.62 (DQ30); also elsewhere on the board
D31: U3.64 (DQ31), U4.64 (DQ31), U5.64 (DQ31), U6.64 (DQ31); also elsewhere on the board
GND: U3.1 (GND), U3.39 (GND), U3.72 (GND), U4.1 (GND), U4.39 (GND), U4.72 (GND), U5.1 (GND), U5.39 (GND), U5.72 (GND), U6.1 (GND), U6.39 (GND), U6.72 (GND); also elsewhere on the board
MA0: U3.12 (A0), U4.12 (A0), U5.12 (A0), U6.12 (A0); also elsewhere on the board
MA1: U3.13 (A1), U4.13 (A1), U5.13 (A1), U6.13 (A1); also elsewhere on the board
MA2: U3.14 (A2), U4.14 (A2), U5.14 (A2), U6.14 (A2); also elsewhere on the board
MA3: U3.15 (A3), U4.15 (A3), U5.15 (A3), U6.15 (A3); also elsewhere on the board
MA4: U3.16 (A4), U4.16 (A4), U5.16 (A4), U6.16 (A4); also elsewhere on the board
MA5: U3.17 (A5), U4.17 (A5), U5.17 (A5), U6.17 (A5); also elsewhere on the board
MA6: U3.18 (A6), U4.18 (A6), U5.18 (A6), U6.18 (A6); also elsewhere on the board
MA7: U3.28 (A7), U4.28 (A7), U5.28 (A7), U6.28 (A7); also elsewhere on the board
MA8: U3.31 (A8), U4.31 (A8), U5.31 (A8), U6.31 (A8); also elsewhere on the board
MA9: U3.32 (A9), U4.32 (A9), U5.32 (A9), U6.32 (A9); also elsewhere on the board
MA10: U3.19 (A10), U4.19 (A10), U5.19 (A10), U6.19 (A10); also elsewhere on the board
MA11: U3.29 (A11), U4.29 (A11), U5.29 (A11), U6.29 (A11); also elsewhere on the board

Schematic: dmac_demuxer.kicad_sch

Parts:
C61, C62, C63, C64, C65, C66: 100n; C_Disc_D4.3mm_W1.9mm_P5.00mm
U41, U42, U44: 74LS245; DIP-20_W7.62mm_Socket
U43, U45: 74LS573; DIP-20_W7.62mm_Socket

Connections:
+5V: C61.2, C62.2, C63.2, C64.2, C65.2, C66.2, U41.20 (VCC), U42.20 (VCC), U43.20 (VCC), U44.20 (VCC), U45.20 (VCC); also elsewhere on the board
/dmac/MUX0: U42.2 (A0), U43.2 (D0); also elsewhere on the board
/dmac/MUX1: U42.3 (A1), U43.3 (D1); also elsewhere on the board
/dmac/MUX2: U42.4 (A2), U43.4 (D2); also elsewhere on the board
/dmac/MUX3: U42.5 (A3), U43.5 (D3); also elsewhere on the board
/dmac/MUX4: U42.6 (A4), U43.6 (D4); also elsewhere on the board
/dmac/MUX5: U42.7 (A5), U43.7 (D5); also elsewhere on the board
/dmac/MUX6: U42.8 (A6), U43.8 (D6); also elsewhere on the board
/dmac/MUX7: U42.9 (A7), U43.9 (D7); also elsewhere on the board
/dmac/MUX8: U44.2 (A0), U45.2 (D0); also elsewhere on the board
/dmac/MUX9: U44.3 (A1), U45.3 (D1); also elsewhere on the board
/dmac/MUX10: U44.4 (A2), U45.4 (D2); also elsewhere on the board
/dmac/MUX11: U44.5 (A3), U45.5 (D3); also elsewhere on the board
/dmac/MUX12: U44.6 (A4), U45.6 (D4); also elsewhere on the board
/dmac/MUX13: U44.7 (A5), U45.7 (D5); also elsewhere on the board
/dmac/MUX14: U44.8 (A6), U45.8 (D6); also elsewhere on the board
/dmac/MUX15: U44.9 (A7), U45.9 (D7); also elsewhere on the board
/dmac/demuxer/UAS: U43.11 (Load), U45.11 (Load)
/dmac/demuxer/~DBEN: U42.19 (CE), U44.19 (CE)
/dmac/demuxer/~DDIR: U42.1 (A->B), U44.1 (A->B)
/dmac/demuxer/~HIBYTE: U41.19 (CE)
/dmac/demuxer/~OWN: U43.1 (OE), U45.1 (OE)
A8: U43.19 (Q0); also elsewhere on the board
A9: U43.18 (Q1); also elsewhere on the board
A10: U43.17 (Q2); also elsewhere on the board
A11: U43.16 (Q3); also elsewhere on the board
A12: U43.15 (Q4); also elsewhere on the board
A13: U43.14 (Q5); also elsewhere on the board
A14: U43.13 (Q6); also elsewhere on the board
A15: U43.12 (Q7); also elsewhere on the board
A16: U45.19 (Q0); also elsewhere on the board
A17: U45.18 (Q1); also elsewhere on the board
A18: U45.17 (Q2); also elsewhere on the board
A19: U45.16 (Q3); also elsewhere on the board
A20: U45.15 (Q4); also elsewhere on the board
A21: U45.14 (Q5); also elsewhere on the board
A22: U45.13 (Q6); also elsewhere on the board
A23: U45.12 (Q7); also elsewhere on the board
D16: U41.2 (A0), U42.18 (B0); also elsewhere on the board
D17: U41.3 (A1), U42.17 (B1); also elsewhere on the board
D18: U41.4 (A2), U42.16 (B2); also elsewhere on the board
D19: U41.5 (A3), U42.15 (B3); also elsewhere on the board
D20: U41.6 (A4), U42.14 (B4); also elsewhere on the board
D21: U41.7 (A5), U42.13 (B5); also elsewhere on the board
D22: U41.8 (A6), U42.12 (B6); also elsewhere on the board
D23: U41.9 (A7), U42.11 (B7); also elsewhere on the board
D24: U41.18 (B0), U44.18 (B0); also elsewhere on the board
D25: U41.17 (B1), U44.17 (B1); also elsewhere on the board
D26: U41.16 (B2), U44.16 (B2); also elsewhere on the board
D27: U41.15 (B3), U44.15 (B3); also elsewhere on the board
D28: U41.14 (B4), U44.14 (B4); also elsewhere on the board
D29: U41.13 (B5), U44.13 (B5); also elsewhere on the board
D30: U41.12 (B6), U44.12 (B6); also elsewhere on the board
D31: U41.11 (B7), U44.11 (B7); also elsewhere on the board
GND: C61.1, C62.1, C63.1, C64.1, C65.1, C66.1, U41.10 (GND), U42.10 (GND), U43.10 (GND), U44.10 (GND), U45.10 (GND); also elsewhere on the board
R/~W: U41.1 (A->B); also elsewhere on the board

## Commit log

2024-01-19 Migration: migration from kms1212/ehbc
    Migration from kms1212/ehbc
    Project sanity is not tested.
2024-03-17 push
2024-09-29 Renamed CMC to SCU, changed verification method to cocotb, and modified pcb schematic
2024-11-10 Added timer and interrupt controller capability to SCU
